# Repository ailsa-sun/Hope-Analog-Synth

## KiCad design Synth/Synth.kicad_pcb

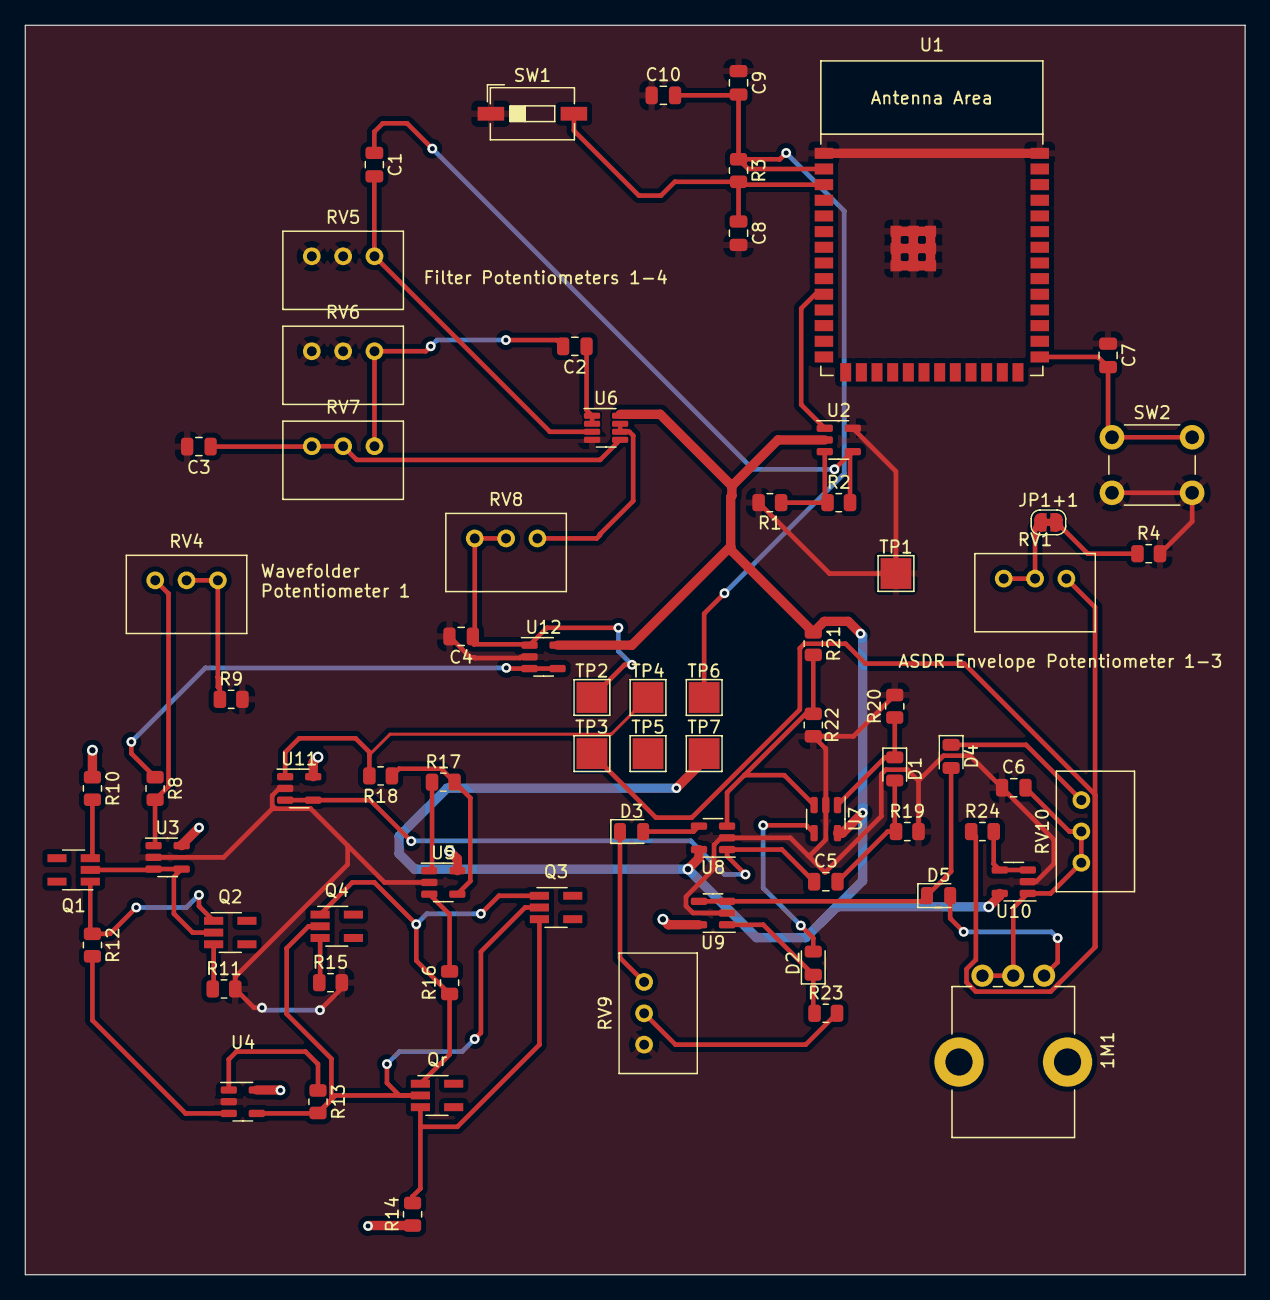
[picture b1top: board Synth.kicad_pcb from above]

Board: 2 copper layers, 98.9 x 101.3 mm, 72 parts (0 on the bottom side), 48 nets.

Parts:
1M1: R_Potentiometer; Potentiometer_Bourns_PTV09A-1_Single_Vertical
C1, C2, C3, C4: C; C_0805_2012Metric
C5, C6, C10: 1uF; C_0805_2012Metric
C7, C8, C9: 0.1uF; C_0805_2012Metric
D1: D_0805_2012Metric
D2, D3, D4, D5: D; D_0805_2012Metric
JP1+1: SolderJumper_2_Open; SolderJumper-2_P1.3mm_Bridged_RoundedPad1.0x1.5mm
Q1, Q3: PNP; SOT-23-5_HandSoldering
Q2, Q4: NPN; SOT-23-5_HandSoldering
Qr: PNP; SOT-23-5_HandSoldering
R1, R18, R24: 1k; R_0805_2012Metric
R2: 1.7k; R_0805_2012Metric
R3, R12, R16, R19: 10k; R_0805_2012Metric
R4, R10, R11, R13, R14, R15: 20k; R_0805_2012Metric
R8, R20, R21, R23: 100k; R_0805_2012Metric
R9: 2k; R_0805_2012Metric
R17: 220k; R_0805_2012Metric
R22: 47k; R_0805_2012Metric
RV1, RV4: 20k; Potentiometer_Bourns_3299W_Vertical
RV5, RV6, RV7, RV8: R_Potentiometer; Potentiometer_Bourns_3299W_Vertical
RV9: 100k; Potentiometer_Bourns_3299W_Vertical
RV10: 1M; Potentiometer_Bourns_3299W_Vertical
SW1: Reset; SW_DIP_SPSTx01_Slide_6.7x4.1mm_W6.73mm_P2.54mm_LowProfile_J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
SW2: Boot; SW_PUSH_6mm_H7.3mm
TP1, TP2, TP3, TP4, TP5, TP6, TP7: TestPoint; TestPoint_Pad_2.5x2.5mm
U1: ESP32-S2-SOLO
U2, U3, U4, U5, U7, U8, U9, U10, U11, U12: LM321; SOT-23-5
U6: Opamp_Dual; TSOT-23-8

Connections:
+3.3V: C9.2, C10.2, R3.1, TP6.1, U1.2 (3V3)
+12V: R10.1, R14.1, R21.1, TP7.1, U2.2 (V-), U3.5 (V+), U4.5 (V+), U5.5 (V+), U6.8 (V+), U7.5 (V+), U8.5 (V+), U9.5 (V+), U10.5 (V+), U11.5 (V+), U12.5 (V+)
ESP Out: C1.1, R2.2, U2.4
Filter Output: C4.1, RV8.2, RV8.3, TP2.1, U12.1 (+)
GND: C3.2, C4.2, C6.1, C7.1, C8.2, C9.1, C10.1, R1.2, R4.2, R9.2, R11.2, R15.2, R19.2, R20.2, R22.2, RV5.2, RV5.3, RV6.2, RV6.3, RV9.3, SW1.1, SW2.2, TP1.1, U1.1 (GND), U1.40 (GND), U1.41 (GND), U2.5 (V+), U3.2 (V-), U4.2 (V-), U5.2 (V-), U6.4 (V-), U7.2 (V-), U8.2 (V-), U9.2 (V-), U10.2 (V-), U11.2 (V-), U12.2 (V-)
LowPass Input: C2.2, RV6.1, RV7.1
unnamed: C5.2, D1.2 (A), R19.1
unnamed: D1.1 (K), R20.1, U7.1 (+)
unnamed: D2.2 (A), U7.4
unnamed: D2.1 (K), R23.1, U9.1 (+)
unnamed: D3.2 (A), U8.4
unnamed: D3.1 (K), RV9.1
unnamed: D4.2 (A), D5.1 (K), U9.3 (-), U9.4
unnamed: D4.1 (K), RV10.1
unnamed: 1M1.3, D5.2 (A)
unnamed: JP1+1.1 (A), RV1.2, RV1.3
unnamed: JP1+1.2 (B), R4.1
unnamed: Q1.2 (B), Q2.2 (B), U3.3 (-), U3.4
unnamed: Q1.1 (C), Q2.1 (C), R12.1
unnamed: Q1.3 (E), R10.2
unnamed: Q2.3 (E), R11.1
unnamed: Q3.2 (B), Q4.2 (B), Qr.2 (B), R13.2, U4.4
unnamed: Q3.1 (C), Q4.1 (C), Qr.1 (C), R16.1
unnamed: Q3.3 (E), Qr.3 (E), R14.2
unnamed: Q4.3 (E), R15.1
unnamed: R9.1, RV4.1, RV4.2
unnamed: R17.2, R18.1, U5.4
unnamed: R23.2, RV9.2
unnamed: C8.1, R3.2, SW1.2, U1.3 (EN)
unnamed: C7.2, SW2.1, U1.27 (GPIO0)
unnamed: U1.10 (GPIO17/U1TXD/ADC2_CH6/DAC_1), U2.1 (+)
unnamed: R1.1, R2.1, U2.3 (-)
unnamed: R8.2, RV4.3, U3.1 (+)
unnamed: R13.1, U4.1 (+)
unnamed: R12.2, U4.3 (-)
unnamed: R17.1, U5.1 (+)
unnamed: R16.2, U5.3 (-)
unnamed: C1.2, RV5.1, U6.3 (+)
unnamed: C2.1, U6.1, U6.2 (-)
unnamed: C3.1, RV7.2, RV7.3, U6.5 (+)
unnamed: RV8.1, U6.6 (-), U6.7
unnamed: R21.2, R22.1, U7.3 (-), U8.3 (-)
unnamed: 1M1.1, 1M1.2, C6.2, RV10.2, RV10.3, U10.1 (+)
unnamed: R24.2, U10.3 (-), U10.4
V_Wavefolder+: R18.2, TP4.1, U11.1 (+)
V_inWF+: R8.1, U12.3 (-), U12.4
V_in_EN+: C5.1, U8.1 (+), U11.3 (-), U11.4
V_out+: R24.1, RV1.1, TP3.1

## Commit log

2024-03-11 added 3-channel mixer
2024-03-13 added in double wavefolder
2024-03-14 adding Ailsa's version w/ high/low pass filter
2024-03-14 commit edits to add buffer to filter
2024-03-14 merged to the same file
2024-03-17 fixed erge stuff fingers crossed
2024-04-09 removed mixer
2024-04-09 more updates, i kinda forgot what
2024-04-11 added some footprints
2024-04-11 changed Pots
2024-04-11 add the layout
2024-04-11 fixed erc errs
2024-04-11 add the ESP
2024-04-11 changed the resistor valuess
2024-04-11 changed the potentiometer footprints
2024-04-11 almost done w layoutgit add *
2024-04-11 made small changes, fixed DRC Errors
2024-04-11 changed hierarchical labels
2024-04-11 Commit the changes to the thing
2024-04-12 fixed
